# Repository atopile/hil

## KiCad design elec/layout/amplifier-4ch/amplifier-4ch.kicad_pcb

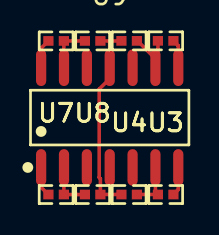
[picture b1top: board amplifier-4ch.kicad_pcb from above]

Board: 2 copper layers, 9 parts (0 on the bottom side), 9 nets.

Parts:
U1, U2, U3, U4, U5, U6, U7, U8: 10kΩ ±1% 62.5mW; R0402-56259e
U9: SOIC-14_L8.7-W3.9-P1.27-LS6.0-BL-988152

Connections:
IN1_: U1.1, U2.2, U9.2
IN2_: U3.1, U4.2, U9.6
IN3_: U5.1, U6.2, U9.9
IN4_: U7.1, U8.2, U9.13
gnd: U2.1, U4.1, U6.1, U8.1, U9.11
line: U7.2, U9.14
line-1: U5.2, U9.8
line-2: U3.2, U9.7
line-3: U1.2, U9.1

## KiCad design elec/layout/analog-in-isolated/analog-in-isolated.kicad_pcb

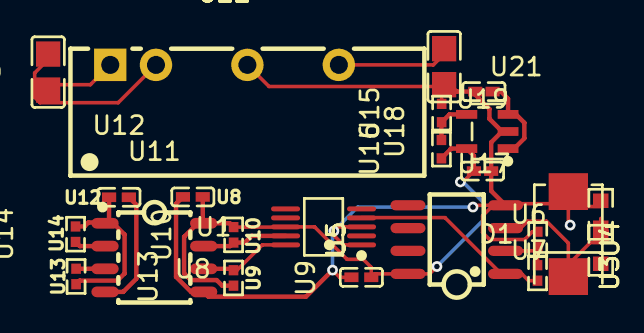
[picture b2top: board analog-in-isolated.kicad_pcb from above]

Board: 2 copper layers, 23 parts (0 on the bottom side), 15 nets.

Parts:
D1: SMB_L4.6-W3.6-LS5.3-RD-330cb3
U1: MSOP-10_L3.0-W3.0-P0.50-LS5.0-BL-752175
U2, U17, U19: 1µF ±10% 25V X5R; C0402-b3ef17
U3, U4, U9, U10, U13, U14, U15, U16: 10kΩ ±1% 62.5mW; R0402-56259e
U5: BW CMRR Ib Vos GBW Iout SR; SOIC-8_L5.0-W4.0-P1.27-LS6.0-BL-294f77
U6, U7: 10kΩ ±1% 100mW; R0603-ebcab9
U8, U12: 100nF ±10% 16V X7R; C0402-b3ef17
U11: SOIC-8_L4.9-W3.9-P1.27-LS6.0-TL-e13595
U18: SOT-23-5_L3.0-W1.7-P0.95-LS2.8-BL
U20: 4.7µF ±10% 25V X5R; C0805-3b2e55
U21: 10µF ±10% 25V X5R; C0805-3b2e55
U22: PWRM-TH_BXXXXS-2WR3-d8b2fb

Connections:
ADJ_NC: U15.1, U16.2, U18.4
gnd: D1.2, U1.1, U1.3, U2.2, U4.1, U5.4, U6.2, U8.2, U11.5, U15.2, U17.2, U18.2, U19.2, U21.2, U22.4
gnd-1: U11.4, U12.2
gnd-2: U20.2, U22.2
hv: U20.1, U22.1
hv-1: U11.1, U12.1, U13.2, U14.2
hv-2: U17.1, U18.1, U18.3, U21.1, U22.6
hv-3: U1.8, U2.1, U5.8, U8.1, U9.2, U10.2, U11.8, U16.1, U18.5, U19.1
inverting_input: U3.1, U4.2, U5.2
line-1: U11.2, U14.1
line-2: U11.3, U13.1
line-3: U1.9, U10.1, U11.7
line-4: D1.1, U5.3, U6.1, U7.2
line-5: U1.10, U9.1, U11.6
output: U1.4, U3.2, U5.1

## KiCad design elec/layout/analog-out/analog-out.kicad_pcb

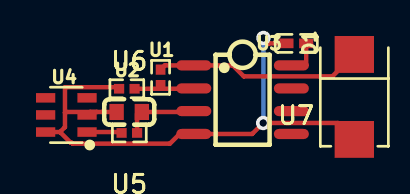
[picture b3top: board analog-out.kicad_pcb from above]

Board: 2 copper layers, 8 parts (0 on the bottom side), 6 nets.

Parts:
D1: SMB_L4.6-W3.6-LS5.3-RD-330cb3
U1, U2: 10kΩ ±1% 62.5mW; R0402-56259e
U3: BW CMRR Ib Vos GBW Iout SR; SOIC-8_L5.0-W4.0-P1.27-LS6.0-BL-294f77
U4: SOT-23-6_L2.9-W1.6-P0.95-LS2.8-BL
U5: 100nF ±10% 50V X7R; C0603-bd72f6
U6: 100kΩ ±1% 62.5mW; R0402-56259e
U7: 1µF ±10% 25V X5R; C0402-b3ef17

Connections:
gnd: D1.2, U2.1, U3.4, U4.2, U4.6, U5.2, U7.2
hv-1: U3.8, U7.1
inverting_input: U1.1, U2.2, U3.2
line-2: U4.1, U6.1
non_inverting_input: U3.3, U5.1, U6.2
output: D1.1, U1.2, U3.1

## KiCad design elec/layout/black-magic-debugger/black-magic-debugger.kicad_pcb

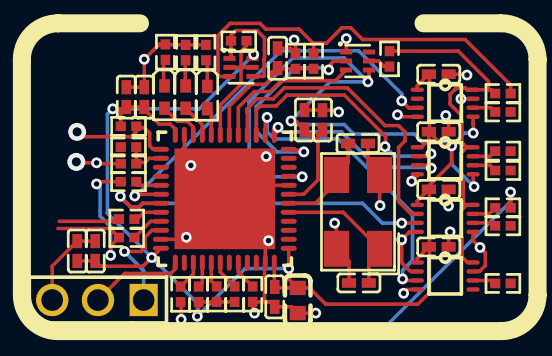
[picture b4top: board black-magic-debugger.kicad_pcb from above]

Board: 2 copper layers, 52 parts (0 on the bottom side), 46 nets.

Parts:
C1: 4.7µF ±10% 25V X5R; C0603-bd72f6
C2: 1µF ±10% 25V X5R; C0402-b3ef17
C3, C4, C5, C6, C7, C8, C11, C12, C13, C14: 100nF ±10% 50V X7R; C0402-b3ef17
C9, C10: 18pF ±5% 50V C0G; C0402-b3ef17
C15: 100nF ±10% 16V X7R; C0402-b3ef17
D1, D2, D3: LED0402-R-RD-049f90
P1: HDR-TH_3P-P2.54-V-M-1-04b1f3
R1, R4, R5, R6, R11, R12, R13, R20, R22: 10kΩ ±1% 62.5mW; R0402-56259e
R2, R3: 22Ω ±1% 62.5mW; R0402-56259e
R7, R8, R9: 1kΩ ±1% 62.5mW; R0402-56259e
R10: 1.5kΩ ±1% 62.5mW; R0402-56259e
R14, R15, R16, R17, R18, R24, R25, R26: 100Ω ±1% 62.5mW; R0402-56259e
R21, R23: 4.7kΩ ±1% 62.5mW; R0402-56259e
U1: UFQFPN-48_L7.0-W7.0-P0.50-BL-EP5.6-10abf8
U2, U3, U4, U5: VSSOP-8_L2.4-W2.1-P0.50-LS3.2-BR-acd3fc
U6, U7: SOT-563-6_L1.6-W1.2-P0.5-LS1.6-BL-d9216f
X1: OSC-SMD_4P-L5.0-W3.2-BL-ee849f

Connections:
B1: R16.1, U4.7
B1-1: R14.1, U3.7
B2: R25.1, U4.6
B2-1: R15.1, U3.6
B2-2: R26.1, U2.6
B2-3: R17.1, U5.6
BOOT0: R1.1, U1.44
D1: U1.17, U7.3
DIR: U1.11, U5.5
G1: R12.1, U1.19, U6.2, U6.5
G1-1: R13.2, U7.5
G2: U1.12, U7.2
NRST: C8.1, U1.7
PA8: R10.2, U1.29
PA11: R2.2, U1.32
PA12: R3.2, U1.33
PA13: P1.1, U1.34
PA14: P1.2, U1.37
PB3: R18.1, U1.39
PB4: R4.1, U1.40
PB5: R5.1, U1.41
PB6: R6.1, U1.42
PB12: R11.1, U1.25
S1: R12.2, U6.1, U6.4
VCCB: R13.1, R24.1, U2.8, U3.8, U4.8, U5.8
anode: D1.1, U1.20
anode-1: D2.1, U1.21
anode-2: D3.1, U1.22
gnd: C1.2, C2.2, C3.2, C4.2, C5.2, C6.2, C7.2, C8.2, C9.2, C10.2, C11.2, C12.2, C13.2, C14.2, C15.2, P1.3, R1.2, R7.2, R8.2, R9.2, R20.2, R22.2, U1.8, U1.23, U1.35, U1.47, U1.49, U2.2, U2.4, U2.7, U3.4, U4.4, U4.5, U5.2, U5.4, U5.7, U7.1, X1.2, X1.4
hv-1: C1.1, C2.1, C3.1, C4.1, C5.1, C6.1, C7.1, C11.1, C12.1, C13.1, C14.1, R4.2, R5.2, R6.2, R11.2, U1.1, U1.9, U1.24, U1.36, U1.48, U2.1, U2.5, U3.1, U3.5, U4.1, U5.1, U6.6, U7.4
hv-2: R23.1, R24.2, U6.3
led0-cathode: D1.2, R7.1
led1-cathode: D2.2, R8.1
led2-cathode: D3.2, R9.1
line: U1.16, U4.2
line-1: U1.15, U3.2
line-2: U1.31, U4.3
line-5: R16.2, R18.2
line-9: U1.13, U3.3
line-10: C15.1, R22.1, R23.2, U1.18
line-11: R20.1, R21.2, U1.26
line-12: U1.30, U2.3
line-13: R3.1, R10.1
line-15: U1.14, U5.3
xin: C9.1, U1.5, X1.1
xout: C10.1, U1.6, X1.3
